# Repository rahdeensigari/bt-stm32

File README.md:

# bt-stm32
An STM32 board with Bluetooth capabilities, made primarily for the sake of practice. I'm making this mainly so I can improve my PCB design skill all around, but mainly to practice making 4-layer boards, as well as to practice SMD soldering. I'm following along with [this](https://www.youtube.com/watch?v=nkHFoxe0mrU) tutorial (with my own changes, of course) to make this board using KiCAD. Firmware wise, I'm currently only using a basic script to flash the onboard LED on and off, but I will change this as I see fit, and all revisions will be updated to the repo.

If you want to make this for whatever reason, I would HIGHLY recommend using an SMD stencil instead of JLCPCB's PCBA, the gerbers and the BOM are in the [production](/production) folder. You can also find the firmware, which is currently just a basic LED blink, in the [firmware](/firmware) folder, and the PCB files themselves in the [pcb](/pcb) folder.

Some general cost estimates (USD):
- PCB: $7.10
- Stencil: $7.22
- LCSC Components: $31.01

If you want to use the RF capabilities, you will need an external antenna. Just search up female U.FL antenna and you will be able to find a lot of antennas that will work perfectly fine.

*Submitted to Forge (Hackclub)*
*Credit to Phil's Lab and Claude*

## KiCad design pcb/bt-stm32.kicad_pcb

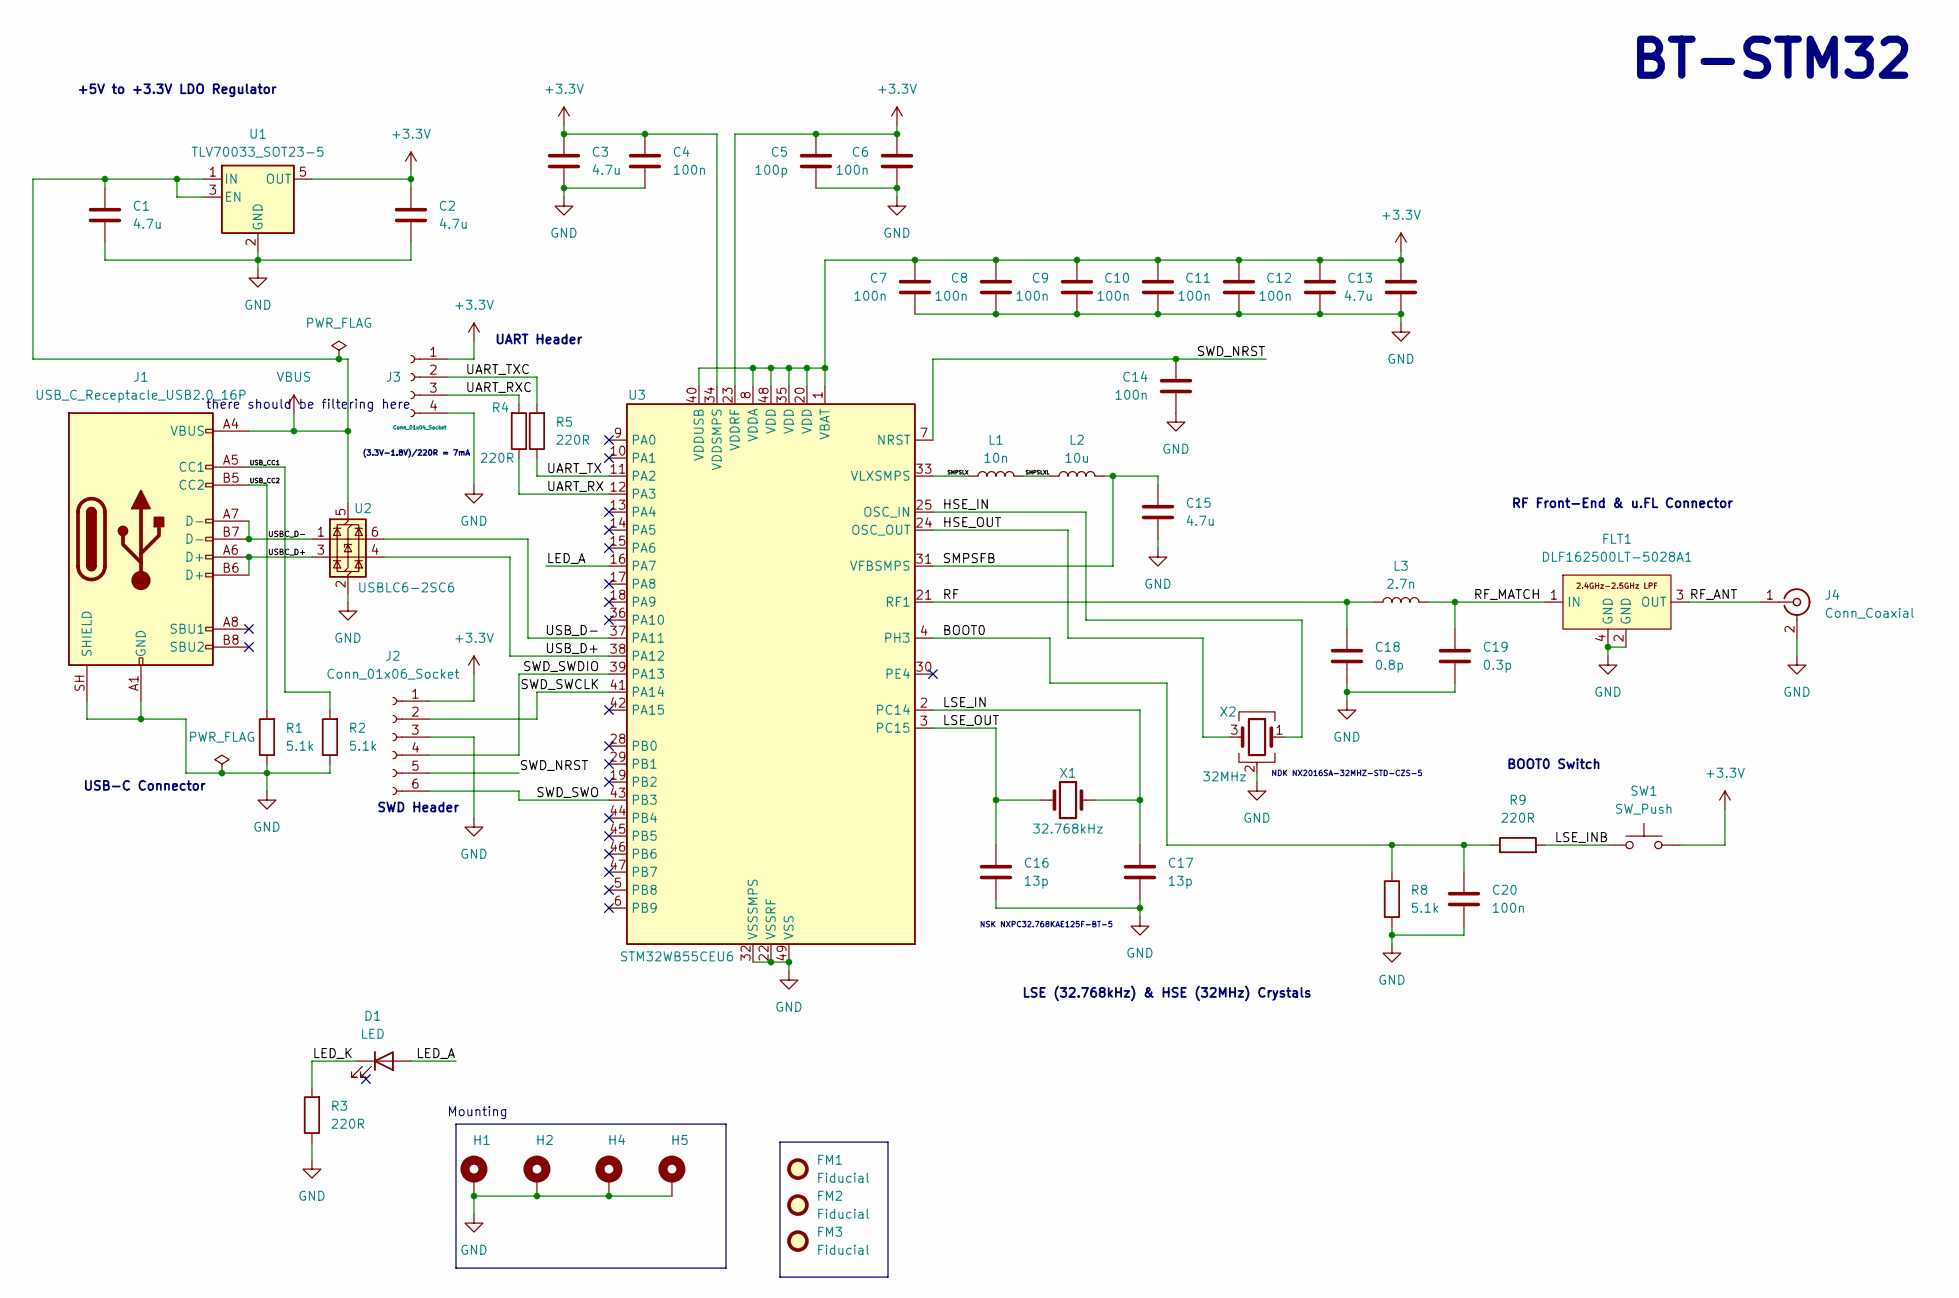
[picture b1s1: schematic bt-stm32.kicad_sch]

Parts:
C1, C2, C3: 4.7u; C_0603_1608Metric; Part Number C1705
C4, C6, C7, C8, C9, C10, C11, C12, C14, C20: 100n; C_0402_1005Metric; Part Number C60474
C5: 100p; C_0402_1005Metric; Part Number C106200
C13, C15: 4.7u; C_0603_1608Metric; Part Number C368809
C16, C17: 13p; C_0402_1005Metric; Part Number C161306
C18: 0.8p; C_0402_1005Metric; Part Number C88902
C19: 0.3p; C_0402_1005Metric; Part Number C76909
D1: LED; LED_0402_1005Metric; Part Number C21260817
FLT1: DLF162500LT-5028A1; Part Number C531364
FM1, FM2, FM3: Fiducial; Fiducial_1mm_Mask2mm
H1, H2, H4, H5: MountingHole_Pad; MountingHole_2.2mm_M2_Pad_Via
J1: USB_C_Receptacle_USB2.0_16P; USB_C_Receptacle_HCTL_HC-TYPE-C-16P-01A; Part Number C2894897
J2: Conn_01x06_Socket; PinHeader_1x06_P1.27mm_Vertical; Part Number C22438072
J3: Conn_01x04_Socket; PinHeader_1x04_P1.27mm_Vertical; Part Number C492398
J4: Conn_Coaxial; U.FL_Hirose_U.FL-R-SMT-1_Vertical; Part Number C598199
L1: 10n; L_0402_1005Metric; Part Number C184029
L2: 10u; L_0805_2012Metric; Part Number C963809
L3: 2.7n; L_0402_1005Metric; Part Number C77108
R1, R2, R8: 5.1k; R_0402_1005Metric; Part Number C105872
R3, R4, R5, R9: 220R; R_0402_1005Metric; Part Number C25091
SW1: SW_Push; SMD,4x3mm; Part Number C49234124
U1: TLV70033_SOT23-5; SOT-23-5; Part Number C11337
U2: USBLC6-2SC6; SOT-23-6; Part Number C7519
U3: STM32WB55CEU6; QFN-48-1EP_7x7mm_P0.5mm_EP5.6x5.6mm; Part Number C911135
X1: 32.768kHz; Crystal_SMD_2012-2Pin_2.0x1.2mm; Part Number C54930595
X2: 32MHz; Crystal_SMD_2016-4Pin_2.0x1.6mm; Part Number C843260

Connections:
+3.3V: C2.1, C3.1, C4.1, C5.1, C6.1, C7.1, C8.1, C9.1, C10.1, C11.1, C12.1, C13.1, J2.1, J3.1, SW1.2, U1.5 (OUT), U3.1 (VBAT), U3.8 (VDDA), U3.20 (VDD), U3.23 (VDDRF), U3.34 (VDDSMPS), U3.35 (VDD), U3.40 (VDDUSB), U3.48 (VDD)
/BOOT0: C20.1, R8.1, R9.1, U3.4 (PH3)
/HSE_IN: U3.25 (OSC_IN), X2.1
/HSE_OUT: U3.24 (OSC_OUT), X2.3
/LED_A: D1.2 (A), U3.16 (PA7)
/LED_K: D1.1 (K), R3.2
/LSE_IN: C17.1, U3.2 (PC14), X1.1
/LSE_INB: R9.2, SW1.1
/LSE_OUT: C16.1, U3.3 (PC15), X1.2
/RF: C18.1, L3.2, U3.21 (RF1)
/RF_ANT: FLT1.3 (OUT), J4.1 (In)
/RF_MATCH: C19.1, FLT1.1 (IN), L3.1
/SMPSFB: C15.1, L2.1, U3.31 (VFBSMPS)
/SMPSLX: L1.2, U3.33 (VLXSMPS)
/SMPSLXL: L1.1, L2.2
/SWD_NRST: C14.1, J2.5, U3.7 (NRST)
/SWD_SWCLK: J2.2, U3.41 (PA14)
/SWD_SWDIO: J2.4, U3.39 (PA13)
/SWD_SWO: J2.6, U3.43 (PB3)
/UART_RX: R4.1, U3.12 (PA3)
/UART_RXC: J3.3, R4.2
/UART_TX: R5.1, U3.11 (PA2)
/UART_TXC: J3.2, R5.2
/USBC_D+: J1.A6 (D+), J1.B6 (D+), U2.3 (I/O2)
/USBC_D-: J1.A7 (D-), J1.B7 (D-), U2.1 (I/O1)
/USB_CC1: J1.A5 (CC1), R2.2
/USB_CC2: J1.B5 (CC2), R1.2
/USB_D+: U2.4 (I/O2), U3.38 (PA12)
/USB_D-: U2.6 (I/O1), U3.37 (PA11)
GND: C1.2, C2.2, C3.2, C4.2, C5.2, C6.2, C7.2, C8.2, C9.2, C10.2, C11.2, C12.2, C13.2, C14.2, C15.2, C16.2, C17.2, C18.2, C19.2, C20.2, FLT1.2 (GND), FLT1.4 (GND), H1.1 (1_1), H2.1 (1_1), H4.1 (1_1), H5.1 (1_1), J1.A1 (GND), J1.A12 (GND), J1.B1 (GND), J1.B12 (GND), J1.SH (SHIELD), J2.3, J3.4, J4.2 (Ext), R1.1, R2.1, R3.1, R8.2, U1.2 (GND), U2.2 (GND), U3.22 (VSSRF), U3.32 (VSSSMPS), U3.49 (VSS), X2.2 (G), X2.4 (G)
VBUS: C1.1, J1.A4 (VBUS), J1.A9 (VBUS), J1.B4 (VBUS), J1.B9 (VBUS), U1.1 (IN), U1.3 (EN), U2.5 (VBUS)

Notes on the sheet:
USB-C Connector
NSK NXPC32.768KAE125F-BT-5
UART Header
Mounting
there should be filtering here
BT-STM32
+5V to +3.3V LDO Regulator
SWD Header
(3.3V-1.8V)/220R = 7mA
NDK NX2016SA-32MHZ-STD-CZS-5
RF Front-End & u.FL Connector
LSE (32.768kHz) & HSE (32MHz) Crystals
BOOT0 Switch

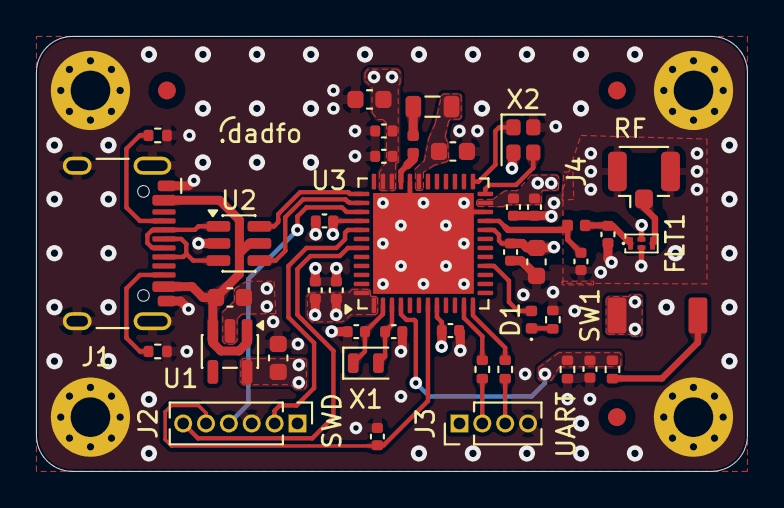
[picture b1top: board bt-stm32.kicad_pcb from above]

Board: 4 copper layers, 39.5 x 24.2 mm, 49 parts (0 on the bottom side), 31 nets.

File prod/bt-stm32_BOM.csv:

"Reference","Qty","Value","DNP","Exclude from BOM","Exclude from Board","Footprint","Datasheet","Manufacturer","Part Number","Link"
"C1,C2,C3,C13,C15","5","4.7u","","","","Capacitor_SMD:C_0603_1608Metric","","Samsung Electro-Mechanics","C1705,C368809","https://www.lcsc.com/product-detail/C1705.html?s_z=n_q_t_cap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,https://www.lcsc.com/product-detail/C368809.html?s_z=n_q_t_c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"
"C4,C6,C7,C8,C9,C10,C11,C12,C14,C20","10","100n","","","","Capacitor_SMD:C_0402_1005Metric","","Walsin","C152819","https://www.lcsc.com/product-detail/C152819.html?s_z=n_q_t_c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"
"C5","1","100p","","","","Capacitor_SMD:C_0402_1005Metric","","YAGEO","C106200","https://www.lcsc.com/product-detail/C106200.html?s_z=n_q_t_c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"
"C16,C17","2","13p","","","","Capacitor_SMD:C_0402_1005Metric","","muRata","C161306","https://www.lcsc.com/product-detail/C161306.html?s_z=n_q_t_c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"
"C18","1","0.8p","","","","Capacitor_SMD:C_0402_1005Metric","","muRata","C88902","https://www.lcsc.com/product-detail/C88902.html?s_z=n_q_t_ca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"
"C19","1","0.3p","","","","Capacitor_SMD:C_0402_1005Metric","","muRata","C76909","https://www.lcsc.com/product-detail/C76909.html?s_z=n_q_t_ca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"
"D1","1","LED","","","","LED_SMD:LED_0402_1005Metric","","YONGYUTAI","C21260817","https://www.lcsc.com/product-detail/C21260817.html?s_z=n_q_t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"
"FLT1","1","DLF162500LT-5028A1","","","","CustomFootprints:DLF162500LT-5028A1","https://product.tdk.com/en/system/files/dam/doc/product/rf/r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","TDK","C531364","https://www.lcsc.com/product-detail/C531364.html?s_z=n_q_DLF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"
"J1","1","USB_C_Receptacle_USB2.0_16P","","","","Connector_USB:USB_C_Receptacle_HCTL_HC-TYPE-C-16P-01A","https://www.usb.org/sites/default/files/documents/usb_type-c.zip","HCTL","C2894897","https://www.lcsc.com/product-detail/C2894897.html?spm=wm.fly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"
"J2","1","Conn_01x06_Socket","","","","Connector_PinHeader_1.27mm:PinHeader_1x06_P1.27mm_Vertical","","hanxia","HX PM1.27-1x6P ZC","https://www.lcsc.com/product-detail/C22438072.html?spm=wm.fl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"
"J3","1","Conn_01x04_Socket","","","","Connector_PinHeader_1.27mm:PinHeader_1x04_P1.27mm_Vertical","","Hong Cheng","C42163122","https://www.lcsc.com/product-detail/C42163122.html?spm=wm.fl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"
"J4","1","Conn_Coaxial","","","","Connector_Coaxial:U.FL_Hirose_U.FL-R-SMT-1_Vertical","","HRS","C598199","https://www.lcsc.com/product-detail/C598199.html?s_z=s_undef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"
"L1","1","10n","","","","Inductor_SMD:L_0402_1005Metric","","muRata","C184029","https://www.lcsc.com/product-detail/C184029.html?s_z=n_q_t_i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"
"L2","1","10u","","","","Inductor_SMD:L_0805_2012Metric","","HYHONGYEX","C963809","https://www.lcsc.com/product-detail/C963809.html?s_z=n_q_C96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"
"L3","1","2.7n","","","","Inductor_SMD:L_0402_1005Metric","","muRata","C77108","https://www.lcsc.com/product-detail/C77108.html?s_z=s_p_LQG1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"
"R1,R2,R8","3","5.1k","","","","Resistor_SMD:R_0402_1005Metric","","YAGEO","C105872","https://www.lcsc.com/product-detail/C105872.html?s_z=n_q_t_r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"
"R3,R4,R5,R9","4","220R","","","","Resistor_SMD:R_0402_1005Metric","","UNI-ROYAL","C25091","https://www.lcsc.com/product-detail/C25091.html?s_z=n_q_t_re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"
"SW1","1","SW_Push","","","","CustomFootprints:SMD,4x3mm","","hanxia","C49234124","https://www.lcsc.com/product-detail/C49234124.html?s_z=n_q_t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"
"U1","1","TLV70033_SOT23-5","","","","Package_TO_SOT_SMD:SOT-23-5","http://www.ti.com/lit/ds/symlink/tlv700.pdf","TI","C11337","https://www.lcsc.com/product-detail/C11337.html?s_z=n_q_t_ld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"
"U2","1","USBLC6-2SC6","","","","Package_TO_SOT_SMD:SOT-23-6","https://www.st.com/resource/en/datasheet/usblc6-2.pdf","ST","C7519","https://www.lcsc.com/product-detail/C7519.html?s_z=n_q_USBLC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"
"U3","1","STM32WB55CEU6","","","","Package_DFN_QFN:QFN-48-1EP_7x7mm_P0.5mm_EP5.6x5.6mm","https://www.st.com/resource/en/datasheet/stm32wb55ce.pdf","ST","C911135","https://www.lcsc.com/product-detail/C911135.html?s_z=n_q_STM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"
"X1","1","32.768kHz","","","","Crystal:Crystal_SMD_2012-2Pin_2.0x1.2mm","","NSX","C54930595","https://www.lcsc.com/product-detail/C54930595.html?s_z=n_q_N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"
"X2","1","32MHz","","","","Crystal:Crystal_SMD_2016-4Pin_2.0x1.6mm","","NDK","C843260","https://www.lcsc.com/product-detail/C843260.html?s_z=n_q_NDK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"

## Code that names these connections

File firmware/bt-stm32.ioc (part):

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Mcu.Name=STM32WB55CEUx
Mcu.Package=UFQFPN48
Mcu.UserName=STM32WB55CEUx
PA11.Mode=Device
PA11.Signal=USB_DM
PA12.Mode=Device
PA12.Signal=USB_DP
PA13.Mode=Trace_Asynchronous_SW
PA13.Signal=SYS_JTMS-SWDIO
PA14.Mode=Trace_Asynchronous_SW
PA14.Signal=SYS_JTCK-SWCLK
PA2.Mode=Asynchronous
PA2.Signal=LPUART1_TX
PA3.Mode=Asynchronous
PA3.Signal=LPUART1_RX
PA7.GPIOParameters=GPIO_Label
PA7.GPIO_Label=LED
PA7.Signal=GPIO_Output
PB3.Mode=Trace_Asynchronous_SW
PB3.Signal=SYS_JTDO-SWO
PB9.Signal=S_TIM17_CH1
PC14-OSC32_IN.Mode=LSE-External-Oscillator
PC14-OSC32_IN.Signal=RCC_OSC32_IN
PC15-OSC32_OUT.Mode=LSE-External-Oscillator
PC15-OSC32_OUT.Signal=RCC_OSC32_OUT
RCC.HSE_VALUE=8000000
RCC.SYSCLKFreq_VALUE=64000000
RCC.SYSCLKSource=RCC_SYSCLKSOURCE_PLLCLK
board=custom
